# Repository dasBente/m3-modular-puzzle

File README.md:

# m3-modular-puzzle
The aim of this project is the implementation of a modular puzzle system including a default casing and some pre-implemented modules accompanying a controller that enables communication between a desired number of puzzle modules that can be exchanged at will.

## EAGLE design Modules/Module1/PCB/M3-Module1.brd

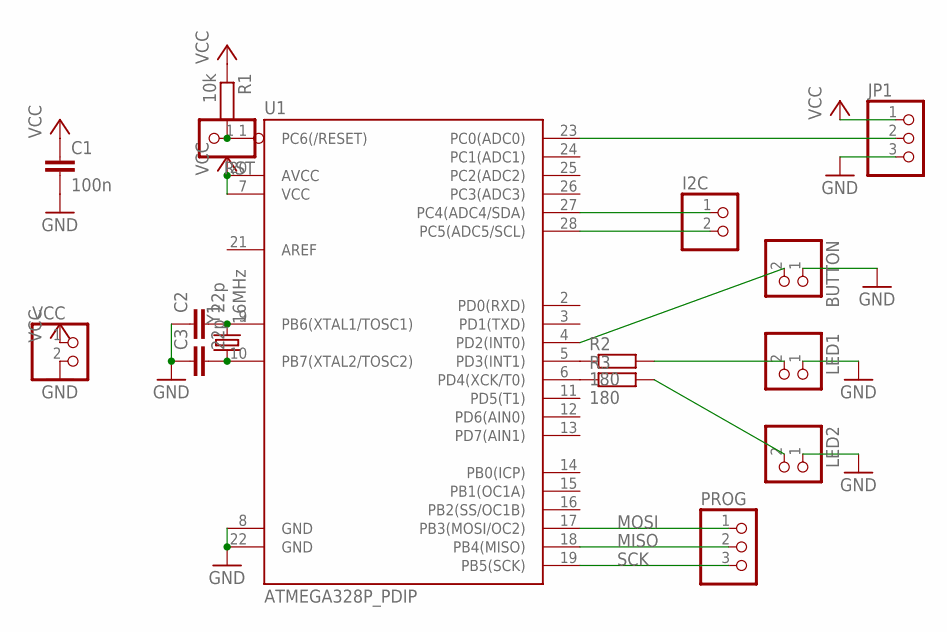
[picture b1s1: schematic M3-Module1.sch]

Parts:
BUTTON: PINHD-1X2; 1X02
C1: 100n; C025-025X050
C2, C3: 22p; C025-025X050
I2C: PINHD-1X2; 1X02
JP1: PINHD-1X3; 1X03
LED1, LED2: PINHD-1X2; 1X02
PROG: PINHD-1X3; 1X03
R1: 10k; 0204/5
R2, R3: 180; 0204/5
RST: PINHD-1X1; 1X01
U1: ATMEGA328P_PDIP; DIL28-3
VCC: PINHD-1X2; 1X02
Y1: 16MHz; HC49US

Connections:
GND: BUTTON.1, C1.2, C2.1, C3.1, JP1.3, LED1.1, LED2.1, U1.8 (GND), U1.22 (GND), VCC.2
MISO: PROG.2, U1.18 (PB4(MISO))
MOSI: PROG.1, U1.17 (PB3(MOSI/OC2))
unnamed: R1.2, RST.1, U1.1 (PC6(/RESET))
unnamed: I2C.1, U1.27 (PC4(ADC4/SDA))
unnamed: I2C.2, U1.28 (PC5(ADC5/SCL))
unnamed: C2.2, U1.9 (PB6(XTAL1/TOSC1)), Y1.2
unnamed: C3.2, U1.10 (PB7(XTAL2/TOSC2)), Y1.1
unnamed: BUTTON.2, U1.4 (PD2(INT0))
unnamed: R2.1, U1.5 (PD3(INT1))
unnamed: R3.1, U1.6 (PD4(XCK/T0))
unnamed: LED1.2, R2.2
unnamed: LED2.2, R3.2
unnamed: JP1.2, U1.23 (PC0(ADC0))
SCK: PROG.3, U1.19 (PB5(SCK))
VCC: C1.1, JP1.1, R1.1, U1.7 (VCC), U1.20 (AVCC), VCC.1

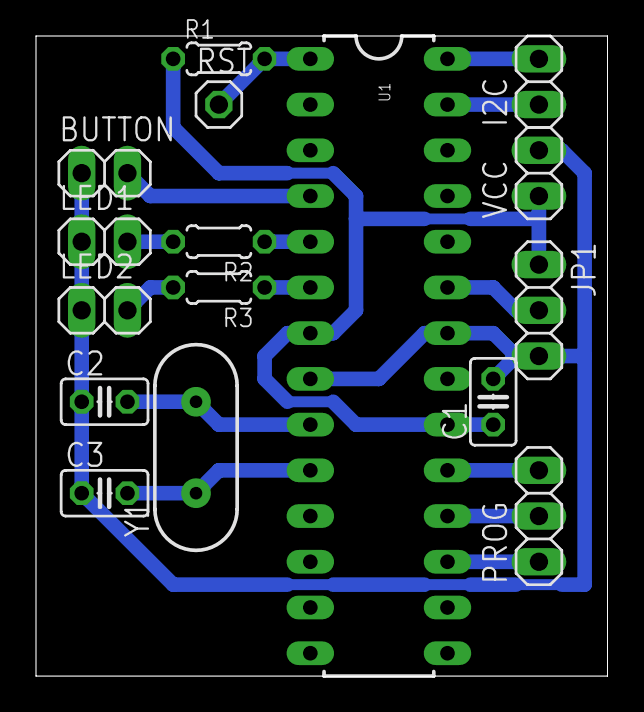
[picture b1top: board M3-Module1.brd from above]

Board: 2 copper layers, 31.8 x 35.6 mm, 16 parts (0 on the bottom side), 16 nets.

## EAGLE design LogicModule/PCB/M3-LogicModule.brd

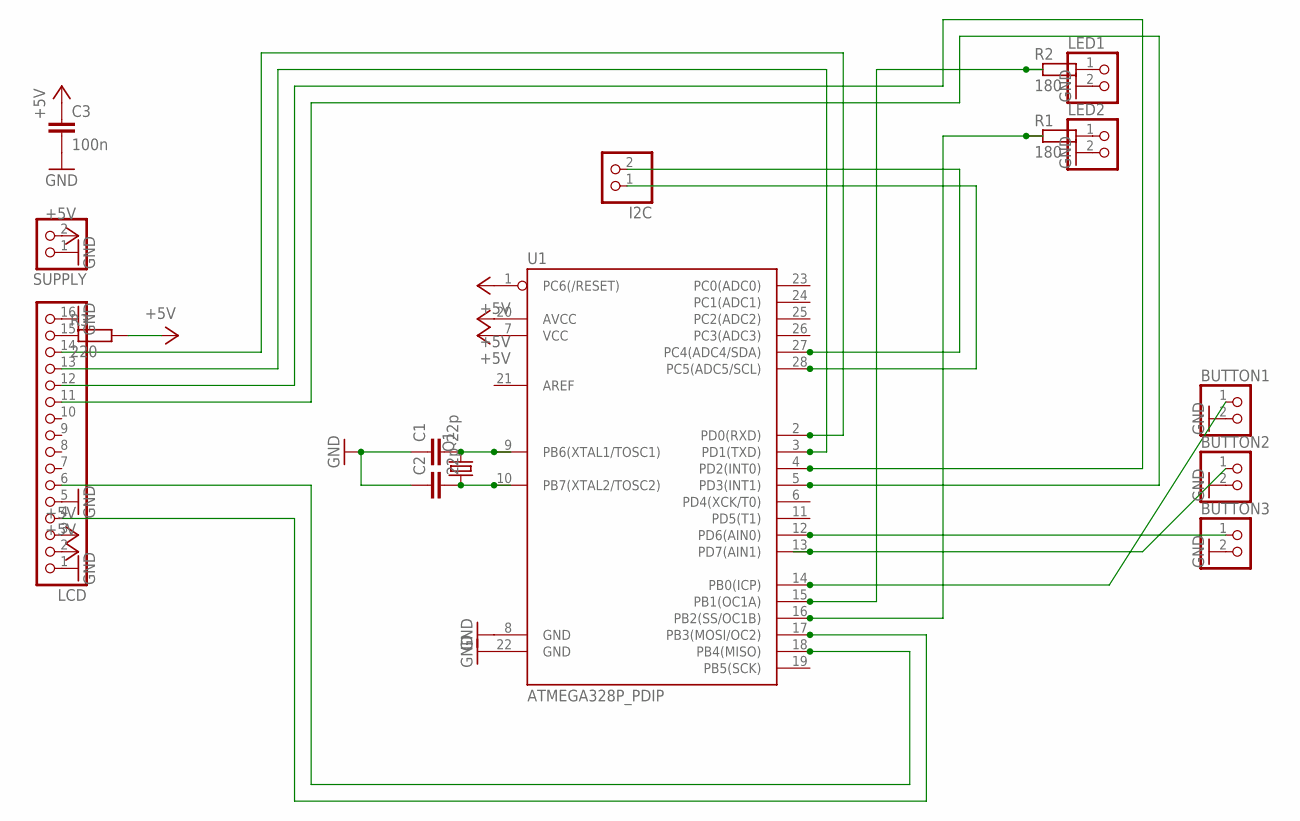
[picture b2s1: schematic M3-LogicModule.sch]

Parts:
BUTTON1, BUTTON2, BUTTON3: PINHD-1X2; 1X02
C1, C2: 22p; C025-025X050
C3: 100n; C2.5-3
I2C: PINHD-1X2; 1X02
LCD: PINHD-1X16; 1X16
LED1, LED2: PINHD-1X2; 1X02
Q1: CRYSTALHC49S; HC49/S
R1, R2: 180; 0309/12
R3: 220; 0309/10
SUPPLY: PINHD-1X2; 1X02
U1: ATMEGA328P_PDIP; DIL28-3

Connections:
+5V: C3.1, LCD.2, LCD.3, R3.2, SUPPLY.2, U1.1 (PC6(/RESET)), U1.7 (VCC), U1.20 (AVCC)
GND: BUTTON1.2, BUTTON2.2, BUTTON3.2, C1.1, C2.1, C3.2, LCD.1, LCD.5, LCD.16, LED1.2, LED2.2, SUPPLY.1, U1.8 (GND), U1.22 (GND)
unnamed: C1.2, Q1.2, U1.9 (PB6(XTAL1/TOSC1))
unnamed: LED2.1, R1.2
unnamed: LED1.1, R2.2
unnamed: R2.1, U1.15 (PB1(OC1A))
unnamed: R1.1, U1.16 (PB2(SS/OC1B))
unnamed: BUTTON1.1, U1.14 (PB0(ICP))
unnamed: BUTTON2.1, U1.13 (PD7(AIN1))
unnamed: BUTTON3.1, U1.12 (PD6(AIN0))
unnamed: C2.2, Q1.1, U1.10 (PB7(XTAL2/TOSC2))
unnamed: LCD.15, R3.1
unnamed: LCD.14, U1.2 (PD0(RXD))
unnamed: LCD.13, U1.3 (PD1(TXD))
unnamed: LCD.12, U1.4 (PD2(INT0))
unnamed: LCD.11, U1.5 (PD3(INT1))
unnamed: LCD.4, U1.17 (PB3(MOSI/OC2))
unnamed: LCD.6, U1.18 (PB4(MISO))
unnamed: I2C.1, U1.28 (PC5(ADC5/SCL))
unnamed: I2C.2, U1.27 (PC4(ADC4/SDA))

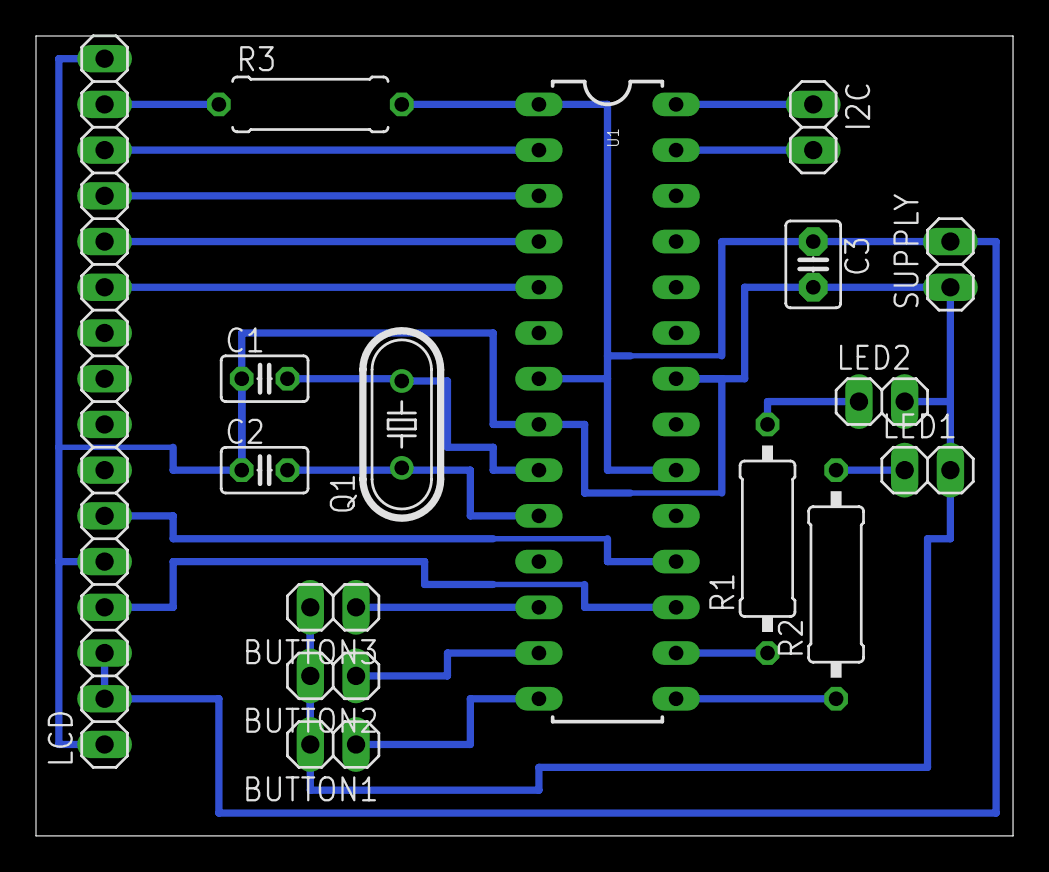
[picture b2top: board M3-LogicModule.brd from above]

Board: 2 copper layers, 54.3 x 44.4 mm, 16 parts (0 on the bottom side), 20 nets.

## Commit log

2016-06-10 Hauptprogrammdatei für Steuereinheit erstellt
    Steuerprogramm für die Steuereinheit erstellt und Verschaltung von
    Mikrocontroller und LCD vorerst in die .ino eingetragen.
2016-06-10 .gitignore hinzugefügt
    Standard .gitignore mit zusätzlichen Einträgen für KiCAD dem Projekt
    hinzugefügt
2016-06-10 .gitignore ergänzt
    Dateien mit Schema *-cache.lib zu .gitignore hinzugefügt.
2016-06-10 KiCAD Projekt für die Steuereinheit angelegt
    Zusätzlich Schaltung von MSP430G2553 mit LCD hinzugefügt.
2016-06-10 Initialisierung für LCD
    Code zur Initialisierung des LCDs
2016-06-11 utils hinzugefügt
    Datei für Hilfsfunktionen und Makros erstellt
2016-06-11 Begrüßung
    Begrüßung für den Nutzer durch den Schriftzug "Modulare Puzzle"
    hinzugefügt. Strings mittels PSTR als PROGMEM um SRAM zu sparen.
2016-06-12 Schaltplan für Steuereinheit angepasst
    Stromquelle auf 5V geändert, zusätzliche Schiene für 3.3V eingefügt.
    Schaltung zum runterpegeln fehlt allerdings noch. Weiterhin habe ich die
    Verschaltung des LCD mit dem Mikrocontroller etwas Kompakter formatiert
    um Platz für zusätzliche Schaltelemente zu schaffen.
2016-06-15 Erstes BoxDesign
    Ein vorläufiges BoxDesign für die Verschalung (3mm Materialdicke)
2016-06-15 Code aufgeräumt für wechsel auf analog
    Der LCD wird durch einen analogen Zeiger an einem Servo-Motor ersetzt,
    der von einem mit Potentiometer festgelegten Punkt herunter zählt. Zu
    diesem Zweck habe ich den bereits bestehenden Code verworfen.
2016-06-15 Anpassung des Schaltplans für analogen Zeiger
    Der analoge Indikator für die verbleibende Zeit soll mittels eines
    Servos realisiert werden, der dementsprechend mit dem mC verschaltet
    werden muss. Der Poti dient dem Einstellen der Rundendauer.
2016-06-15 Auslesen eines Potis implementiert
    Dieser Code entspricht größtenteils dem Codebeispiel "Knob" aus der
    Arduino-Entwicklunksumgebung, da dieses bereits die grundlegende
    Funktionalität abdeckt, den Servo entsprechend der Drehung des Potis
    einzustellen.
2016-06-16 Knopfdruck zum halten des Zählerstandes hinzugefügt
    Durch einen Druckknopf kann jetzt der Wert von "time_remaining"
    festgelegt werden.
2016-06-16 Debug Code hinzugefügt
    Der Code verfügt jetzt über Debugelemente. Explizit deutet die
    On-Board-LED des Genuino Boards hier darauf hin, ob "hold" bereits
    gesetzt wurde.
2016-06-16 inline zu time_to_servo hinzugefügt
    Der Funktion time_to_servo wurde ein inline hinzugefügt.
2016-06-20 enum für den Spielstatus ergänzt
    Das enum GameState soll der Steuerung des Spielzustandes dienen. Es sind
    allerdings vielleicht noch zu viele Zustände enthalten, die ich erstmal
    Sicherheitshalber zugefügt habe, um logische Schritte im Spielfluss
    abzudecken.
2016-06-20 Logik auf GameState abgeändert
    Die Logik des Programmes läuft jetzt durch GameState ab und nicht mehr
    über den buttonState und hold. Weiterhin wurde hold in held umbenannt,
    was die Funktion der Variable als Angabe, ob der Button gehalten wird,
    einfacherer inferierbar machen sollte.
2016-06-20 Serielle Verbindung für Debugging
2016-06-20 Countdowntimer mit Servo
    Der Servo emuliert jetzt einen heruntertickenden Zeiger um die
    verbleibende Spielzeit zu indizieren.
2016-06-22 added protocol documentation
2016-06-22 test
    as
2016-06-22 test finished
2016-06-22 Translated comments from german to english
    For the sake of easier accessibility, the code and commits are to be in
    english from now on. Also, all file- and directorynames have been
    translated.
2016-06-22 Discarded utils.h
2016-06-22 Removed deviance value
    The deviance value that should emulate needle fluctuations is removed
    for now as the current implementation simply does not do anythin,
    probably because of the amount of changes to the value per second.
2016-06-25 Random number added to game start
2016-06-28 First code structure
2016-06-30 Updated README.md to be in english
2016-06-30 Removed match for *-cache.lib
    This file is crucial for retaining the intended look for components in schematics.
2016-06-30 Refactoring of variables and defines
    This commit moves defines and variable definitions to the upper part
    of the code.
2016-06-30 Changed GS_INIT to GS_RESET
    Added changed the name of GS_INIT to the semantically more correct
    GS_RESET, as this state will be used to reset game information.
    Also added changed some of the logic involving game states to fit
    into the new modell using GS_RESET:
    - added reset_game()-Function for resetting game state
    - changed and extended logic in loop()
2016-06-30 Added message to check if serial monito works as intended
2016-06-30 Implemented Indicator for remaining tries
    The player can read from a set of three LEDs how often he can still fail at
    solving one of the puzzle modules.
    This adds another fail state to the game other than running out of time.
    The remaining time can be set by setting the game time:
    - <=120s equals one try
    - <=240s equals two tries
2016-06-30 Created and initialized files for new module
2016-07-01 first electronic schematic
2016-07-04 Initialization of basic Simon module
2016-07-05 ready for test, prototype
2016-07-05 ready for testing, prototype
2016-07-06 Initialization of I2C connection
    This commit sets up the basics of I2C connection between the controller
    and the modules.
    Also, a array to contain module addresses is implemented.
2016-07-06 Implemented module initialization
    Now, the modules are initialized using the init_modules function. The
    modules are reinitialized before each game round to allow swapping
    modules inbetween games.
2016-07-06 Implemented I2C communication
    This commits implements most of the I2C communication for the
    main-controller. This commit still remains to be tested.
2016-07-06 Code update: small resume fix after fail
2016-07-06 folderstructure updated
2016-07-06 testmodule added
2016-07-07 Added Debug messages to monitor I2C
    Some debug messages printed to serial monitoring which (meaningfull)
    packages are received and also indicating whether these are processed
    correctly.
2016-07-07 Fixed bug not updating remaining tries
    Forgot to actually assign the freshly updated number of tries to the
    tries-Variable.
2016-07-07 Updated Schematic
    Added the push button and some LEDs currently used by the main
    controllers programm. Also added bus lines for the SDA and SCL pins
    required for I2C to work.
2016-07-07 Added communication error handling
    Added error handling in case of internal module error. Also refactored
    some of the communication code.
2016-07-14 switched to EAGLE
2016-07-15 Changed refererence to module to address
    Should have already been in some earlier commit.
2016-07-15 Updated .gitignore for use of LaTeX
    Included some .gitignore template for commiting Latex code.
2016-07-15 Manual for Simon
    Added a manual for the Simon module including some basic explanations of
    how permutations work.
2016-07-16 Minor tweak to permutation table
2016-07-16 Initialized Wire connection (for I2C)
2016-07-16 Refactored and added defines
    The defines for the control LEDs have been refactored a bit. Also some
    additional defines for additional LEDs and the I2C-address of the module
    have been added.
2016-07-16 Added GameState enum
    As with MainController.ino, this enum keeps track of the current state
    of the game.
2016-07-16 Initialized game state LEDs
2016-07-16 Changed assignment for semantic clarity
    As the number of sequences to solve is tracked by the amount of 1-bits
    in to_solve (e.g. 0b11 means there are two sequences that still need to
    be solved), assigning values only in binary is semantically more clear.
2016-07-16 Rename of Defines
    Should have already happened a few commits ago!
2016-07-16 Added a code for keeping track of permutations
    Colors are represented by 2 bits each in a byte according to the
    defines. The value for each color also represents the colors default
    position in the byte, e.g the first two bit of a permutation are 0b11,
    then this represents a permutation mapping red to yellow.
2016-07-16 Added a footnote to the manual (of Simon)
2016-07-16 Updated manual to contain win/lose conditions
2016-07-16 Fixed permutations
2016-07-16 Changed pins assigned to solved and fail LEDs
2016-07-16 Added define for I2C Protocol elements
2016-07-16 Changed to BUSY
2016-07-16 Changed encryption of permutations
    This is easier to process later on
2016-07-16 Added Receive and Request Event for Wire
2016-07-16 Added game logic
    Button Handling, Blinking, initialization etc.
2016-07-16 Removed unused variable
2016-07-16 Forgot these two commits ago
2016-07-16 Added some Debug commands
    This helps to monitor the module via serial connection.
2016-07-17 Labeled permutations (with comments)
2016-07-17 Fixed compose
    Should now correctly compose permutations
2016-07-17 Some additional Debug informations and refactoring
2016-07-17 Some more refactoring
2016-07-17 Toggled off debug mode
2016-07-17 Changed microcontrollers Pinlayout (in the code)
    Changes in the KiCAD file are inbound too. Probably including a switch
    to Eagle CAD
2016-07-17 Small indentation and whitespace changes
2016-07-17 Added some more feedback in case of win/loss
    Also included is the increase in timer speed if the player caused a fail
    to trigger.
2016-07-17 added LogicModule files
2016-07-18 Switched KiCAD for eagle project
2016-07-18 Switched to Pull-up. Fixed Blink.
2016-07-18 Face of the clock to be laserengraved
2016-07-19 small fix + cleanup
2016-07-19 Refactoring and additions
    Added call to set_RNG_LEDs to actually set the LEDs (probably forgot
    this one because I was not able to test this).
    Also added additional call to shutdown_modules after loss through
    running out of lives. Refactored code accordingly.
    Lastly, reduced the number of modules on internal module error (win
    state) to ensure that the player is not punished for any module
2016-07-20 Hopefully fixed module solves
    A bug would trigger GS_WON when one module signaled solve, as the module will keep sending solve. Redefined win state.
2016-07-20 Final Box-Design
    The final box-Design for the case and the modules
2016-07-21 Added support for needy modules
    A needy module is any kind of module that can not actually be solved but
    instead require occasional attention by the player. In the game start
    phase, a needy module sends a 2 to acknowledge the main controllers game
    start request. The controller thus knows, that the module is needy and
    does not count towards a full solution of the puzzle at hand. The code
    changes in this commit have not yet been tested.
2016-07-24 Added some details to the face plate for ease of use
    Basically, added stuff so the module can now be cut/engraved in one go.
2016-07-26 Some small changes to the PCB and schematic
2016-07-26 Added custom VisiCut template for logic module
2016-09-19 Added GNU GPL 3.0 License

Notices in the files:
parts and their libraries:
SparkFun-DigitalIC: Licensing: Creative Commons ShareAlike 4.0 International - https://creativecommons.org/licenses/by-sa/4.0
